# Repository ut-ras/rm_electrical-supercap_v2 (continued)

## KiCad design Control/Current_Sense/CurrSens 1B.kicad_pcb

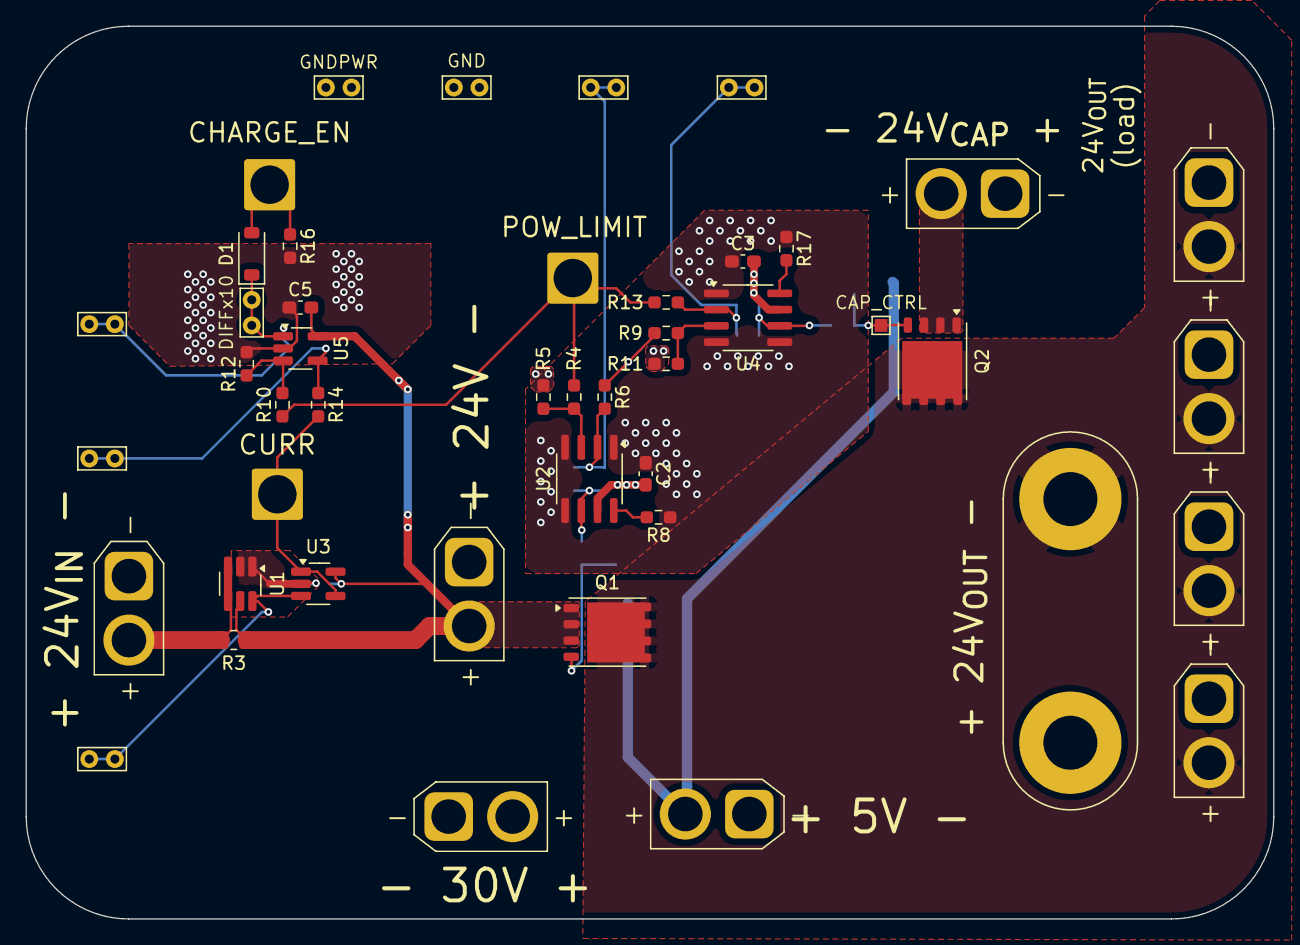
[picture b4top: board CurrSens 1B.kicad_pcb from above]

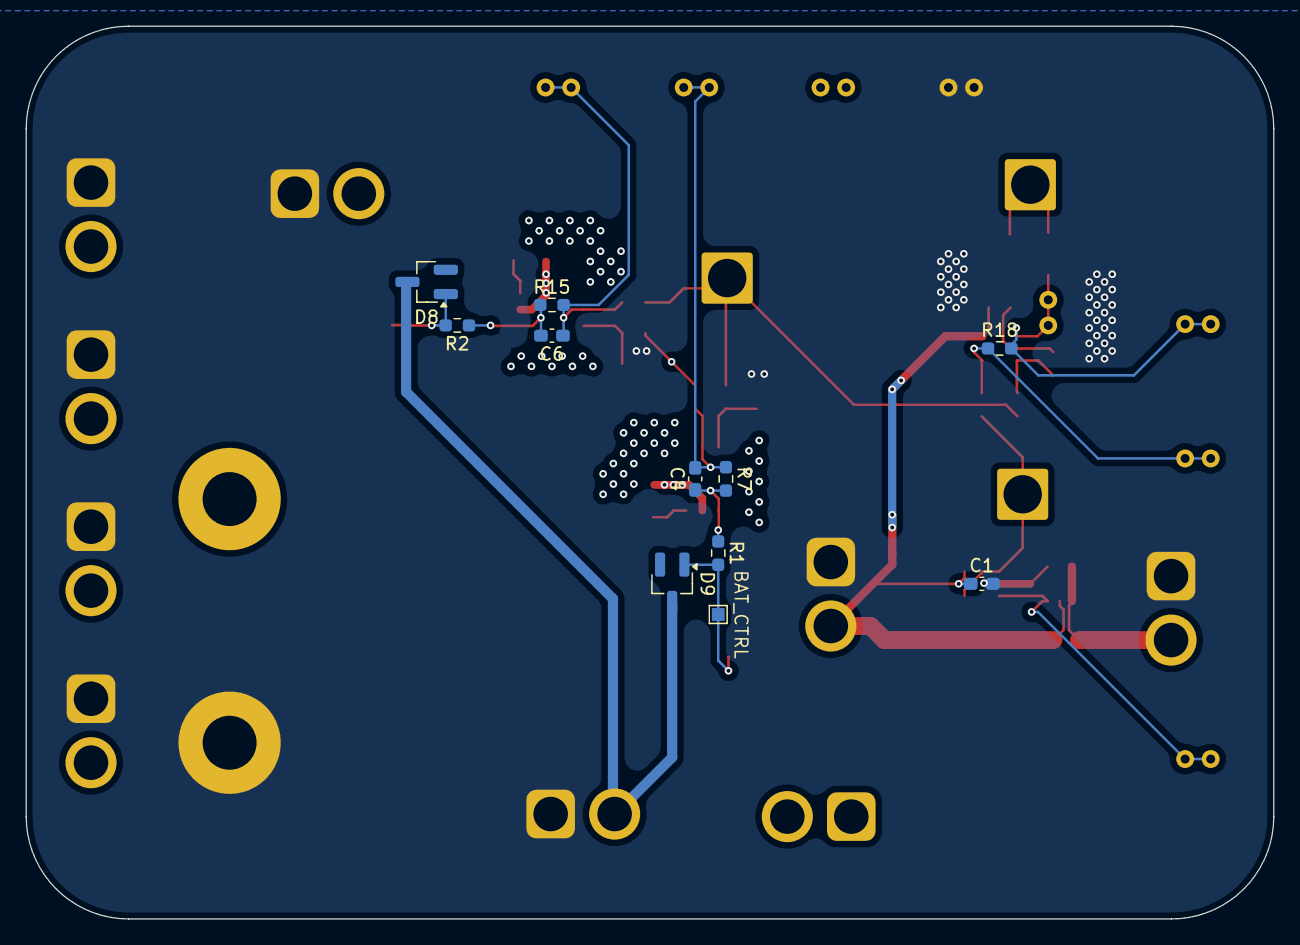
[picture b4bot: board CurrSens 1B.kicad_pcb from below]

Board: 4 copper layers, 97.5 x 69.8 mm, 57 parts (11 on the bottom side), 25 nets.

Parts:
C1, C2, C3, C5: 0.1u; C_0603_1608Metric_Pad1.08x0.95mm_HandSolder
C4, C6: 1000p; C_0603_1608Metric_Pad1.08x0.95mm_HandSolder
D1: MMSZ4678T1G; D_SOD-123
D8, D9: BAT54; SOT-23_Handsoldering
J1, J2, J10: Conn_01x01_Pin; SolderWire-2.5sqmm_1x01_D2.4mm_OD3.6mm
J3, J6, J7, J9, J11, J12, J13, J14, J15: XT30_F; AMASS_XT30U-F_1x02_P5.0mm_Vertical
J16: Banana; RM_Banana_Jack_2Pin
Q1, Q2: BSC059N04LS6; Infineon_PG-TDSON-8_6.15x5.15mm
R1, R2: 0; R_0603_1608Metric_Pad0.98x0.95mm_HandSolder
R3: 0.02; R_0805_2012Metric_Pad1.20x1.40mm_HandSolder
R4, R6, R9, R13: 1k; R_0603_1608Metric_Pad0.98x0.95mm_HandSolder
R5, R7, R11, R12, R15, R18: 1Meg; R_0603_1608Metric_Pad0.98x0.95mm_HandSolder
R8, R17: 47k; R_0603_1608Metric_Pad0.98x0.95mm_HandSolder
R10, R14: 100k; R_0603_1608Metric_Pad0.98x0.95mm_HandSolder
R16: 15k; R_0603_1608Metric_Pad0.98x0.95mm_HandSolder
TP1, TP2, TP3: V_{DIFF10}; TestPoint_Bridge_Pitch2.0mm_Drill0.7mm
TP4, TP5: V_{DIFF10}; TestPoint_Pad_1.0x1.0mm
TP6: CE_OUT; TestPoint_Bridge_Pitch2.0mm_Drill0.7mm
TP7: CE_IN_NEG; TestPoint_Bridge_Pitch2.0mm_Drill0.7mm
TP8: I_OUT; TestPoint_Bridge_Pitch2.0mm_Drill0.7mm
TP9: CAP_IN_NEG; TestPoint_Bridge_Pitch2.0mm_Drill0.7mm
TP10: BAT_IN_NEG; TestPoint_Bridge_Pitch2.0mm_Drill0.7mm
U1: MAX4073T; SOT-23-6_Handsoldering
U2, U4: OPA551U; SOIC-8_3.9x4.9mm_P1.27mm
U3, U5: TLV9301xDBV; SOT-23-5_HandSoldering

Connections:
+5V: D8.3 (A), D9.3 (A), J12.2
+24V: C1.1, C5.1, J13.2, Q1.1 (S), Q1.2 (S), Q1.3 (S), R3.2, U1.5 (RS-), U3.5 (V+), U5.5 (V+)
/+24V_CAP_IN: J14.2, Q2.1 (S), Q2.2 (S), Q2.3 (S)
/+24_IN: J15.2, R3.1, U1.3 (Vcc), U1.4 (RS+)
/+24_MERGED: J3.2, J6.2, J7.2, J9.2, J16.2, Q1.5 (D), Q2.5 (D)
/BAT_CTRL: C4.2, R1.1, R7.2, U2.6
/BAT_CTRL_R: D9.1 (K), Q1.4 (G), R1.2, TP5.1
/CAP_CTRL: C6.2, R2.1, R15.2, U4.6
/CAP_CTRL_R: D8.1 (K), Q2.4 (G), R2.2, TP4.1
/CHARGE_EN_OUT: D1.2 (A), J10.1, R16.2
/CURR_OUT: J2.1, R6.1, R9.1, R14.1, U3.1, U3.4 (-)
/Current Sense/1+: R4.2, R5.2, U2.3 (+)
/Current Sense/1-: C4.1, R6.2, R7.1, TP10.1, U2.2 (-)
/Current Sense/2+: R9.2, R11.2, U4.3 (+)
/Current Sense/2-: C6.1, R13.2, R15.1, TP9.1, U4.2 (-)
/Current Sense/3+: R10.2, R12.2, U5.3 (+)
/Current Sense/3-: R14.2, R18.1, TP7.1, U5.4 (-)
/Current Sense/CURR_{RAW}: TP8.1, U1.6 (OUT), U3.3 (+)
/Current Sense/DIFF10: D1.1 (K), R18.2, TP1.1, TP6.1, U5.1
/Current Sense/FLAG_{1}: R8.1, U2.8 (Flag)
/Current Sense/FLAG_{2}: R17.1, U4.8 (Flag)
/POW_LIMIT_IN: J1.1, R4.1, R10.1, R13.1
GND: C2.2, C3.2, J11.1, R8.2, R17.2, TP2.1, U2.1 (V-), U2.4 (V-), U2.5 (V-), U4.1 (V-), U4.4 (V-), U4.5 (V-)
GNDPWR: C1.2, C5.2, J3.1, J6.1, J7.1, J9.1, J12.1, J13.1, J14.1, J15.1, J16.1, R5.1, R11.1, R12.1, R16.1, TP3.1, U1.1 (GND), U1.2 (GND), U3.2 (V-), U5.2 (V-)
VCC: C2.1, C3.1, J11.2, U2.7 (V+), U4.7 (V+)

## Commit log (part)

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2025-10-31 Initial organization and commit
2025-10-31 New directories for subcircuits/designs
2025-10-31 add input buck
2025-11-01 Current Sense
2025-11-02 began setup of hierarchial boards for supercap
2025-11-04 added more flesh to overall structure, primarily on converter stage
2025-11-05 finished first pass of general block diagram
2025-11-05 replaced 2p2s caps with full parallel
2025-11-09 created PLECS simulation file, need to figure out what is going on with ringing behavior
2025-11-15 Updated power stage PLECS simulation
2025-11-22 added switch-cycle average model with parameters for constant current control in open loop
2025-11-27 removed unnecessary critical loop
2025-12-20 switched capacitor topology to 4S
2026-01-30 changed converter topology to full-bridge design
2026-02-08 dc/dc converter
2026-02-10 added presentation for professors, updated PLECS models
2026-02-15 began work on adding gate driver circuitry
2026-02-16 Added schematic, footprints, and datasheets for voltage sense
2026-02-20 added symbol libraries and finished gate driver circuitry schematic
2026-02-22 fixed converter section
2026-02-22 housekeeping_2
2026-02-22 MSPM0 Connections
2026-02-22 added mosfet footprints and assigned to switch symbols
2026-02-22 Diff Amp
2026-02-22 housekeeping-added-2
2026-02-22 updated PLECs simulations
2026-02-22 assigned footprints for some passives
2026-02-26 added inductor design file
2026-03-01 12Vmodified
2026-03-01 attempting to push kicad library mosfet sym/foot
2026-03-01 more simulation work + fixed some things in root schematic
2026-03-01 DCDCconverter modified
2026-03-01 wiring connected, now only need msmp0 pinout and footprint assignments
2026-03-01 fixed inductor connection
2026-03-01 decoupling capacitors assigned
2026-03-01 removed v1 files and assigned mouser part numbers
2026-03-02 began layout
2026-03-03 mostly done with first order layout
2026-03-04 I FINALLY FIGURED OUT THE CONTROL SCHEME I NEEDED A SQUARE ROOT
2026-03-06 more changes to sims for reverse engineering
2026-03-06 added sample data to MATLAB
2026-03-06 fixed merge conflict in average mode
2026-03-06 Added program to fit exponential decay function to data points
2026-03-07 critical loops trace
2026-03-08 more controls work
2026-03-08 hopefully: did crit and driver loops for rt half bridge, swapped decoupling caps and Cd/Csmooth 6 and 7 for organization purposes
2026-03-08 bigger trace push before trevor starts
2026-03-08 added linearized model
2026-03-08 Fits curve to two data sets for ease of comparison
2026-03-08 ok hopefully this doesnt break everything, committing after doing in kicadlib submod
2026-03-08 FirmWare
2026-03-08 added mspm0 fp, still need to map pin nets on sym in schematic, in process of doing redesign to min power path
2026-03-09 WORKING SWITCH-CYCLE AVERAGE MODEL LESGOOOOOO
2026-03-10 more screwing around with open loop control
2026-03-11 added toy model
2026-03-11 Created quadratic linearization model
2026-03-11 started work on slides explaining linearization
2026-03-12 updated toy model
2026-03-12 fixing inprogress files from previous commit
2026-03-12 finished PI+FF presentation
2026-03-12 large expansion to explanation powerpoint + some brushing up on toy model
2026-03-12 evil and intimidating file embed
2026-03-12 more slides
2026-03-12 I really need to remember to close PLECS before committing
2026-03-12 identified new issue
2026-03-13 via stitching on fets, fixed sheet pin (not label on parent) for isense, messed around with design
2026-03-14 still trying to get discharging cycle to work
2026-03-21 big progress on layout
2026-03-21 FINISHED EXCEPT FOR FAULT TRACES YIPPEE
2026-03-22 jed irl review
2026-03-23 Fault Code & Pins
    Added the config for the hardware fault handing of the current sensors. When the fault signal falls low all pwm signals and their complements are set to grounod. Additionally the traces for this were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
    Other: Changed some ADC input pins to avoid double use with the launch pad board.
2026-03-24 minor PCB tweaks
2026-03-24 made corners better for switch nodes, hopefully
2026-03-27 cleaned up sections to be repositioned
2026-03-27 started work on reverse charging functionality
2026-03-27 need to see other board
2026-03-28 need to pu v1 to make copy on other desktop
2026-03-28 im so bad at this :skull Vsc+ pour boutta go crazy, the mspm0 pin buses too, idk if i even got what i did right lmao but ill figure it out later
2026-03-28 updated powerpoint
2026-03-29 finished sensitivity theoretical section of powerpoint
2026-03-29 still can't figure out algebraic loop error
2026-03-29 Trevor2.0
2026-03-29 Closed loop transfer function sensitivities
2026-03-29 Sensitivities
2026-03-29 getting paranoid that kicads gonna crash: moved current sense IC and inductor pad assoc. drew rest of main pours for cap charging, gndpwr, etc
2026-03-29 sensitvity errors
2026-03-29 Added Noise
2026-03-29 transfer function moving
2026-03-29 Added sensitivity to last slide
2026-03-29 updated sensitivity
2026-03-29 finished moving files
2026-03-29 finished foundation pours, layout, tp routing along edges. Next: cursed routing I sense IC/H to 3v3, 3v3 to mspm0
2026-03-29 Sensor White Noise Slide
2026-03-30 sync
2026-03-30 removed PI2 control and improved disturbance rejection from PI
2026-04-01 FAULT HANDELR WORKING!!!!
    There is still an issue where the ISR is not running so we currently can't clear the fault but that might be desired.
2026-04-01 inductor design file
2026-04-02 updated PLECs model to use new inductor parameters
2026-04-05 that took a lot longer than i thought and so cursed. looks kinda cool though, finished the H bridge/3v3/mspm0 traces, tried to keep along edges. holding off on via stitching just yet cuz im sure glor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
2026-04-05 small things, trevor checked, awaiting heavenly mandated egan
2026-04-05 glitching out, some stitching
2026-04-05 worked a lil on the FFPI
    Problem with imported math function but the code is saved in a text document called FFPI
2026-04-05 Should I go to my Ex's Choir Concert?
2026-04-05 Trevor is a genius, flipped mspm0 pins, in progress: 3v3 rerouting/redesign, edge pathing, deleting old stuff, etc.
2026-04-10 Matlab for LC filter
2026-04-10 put filters closer to IC's, cleared up some stuff, still gonna have cool cross board bus prob yipee
2026-04-11 Matlab and Excel for Pi filter values, poles, and zero
2026-04-11 matlab
2026-04-11 moved file
2026-04-11 moving files
2026-04-12 done, routed everything, todo: DRC
2026-04-12 updated matlab + Bode plotting
2026-04-12 DRC, cleared up all errors except 2 that are unavoidable with board settings (2 pads on the same ic being too close). Warnings are vast majority of the silkscreen, solder mask type. A few important w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
2026-04-12 small
2026-04-12 starting on V3 :) yipee. finished pours and stuff
2026-04-13 laid out PCB rev C
2026-04-14 finished prelim board layout pending filter inductor redesign
2026-04-14 added parallel capacitance, minor cleanup to design - jed review + approval
2026-04-14 added heatsinks + more bulk capacitance footprints
2026-04-14 added better smoothing behavior to power supplies and op-amps as per application notes, switched resistors to op-amp with higher values
2026-04-14 minor tweaks to model + filter design
2026-04-15 split into separate boards as per regulations
2026-04-15 added more diagnostics for the PI loop
2026-04-15 still need to finish housekeeping power supply footprints
2026-04-15 cleaned up PCB after meeting with BBJ
2026-04-15 created drill files
2026-04-15 BOM stuff
2026-04-16 made some progress on model blowing up
2026-04-16 plotted standalone board and updated KiCAD BOM (not spreadsheet BOM)
2026-04-17 new library updates
2026-04-17 Thx Tim
2026-04-17 added Heath revision
2026-04-21 going to run boost mode back
2026-04-21 beginning work on simulink
2026-04-26 added simulink simulation
2026-05-05 finished power stage modeling powerpoint
2026-05-07 big ahhhh merge + partial bringup guide written
2026-05-09 more bringup guide progress
